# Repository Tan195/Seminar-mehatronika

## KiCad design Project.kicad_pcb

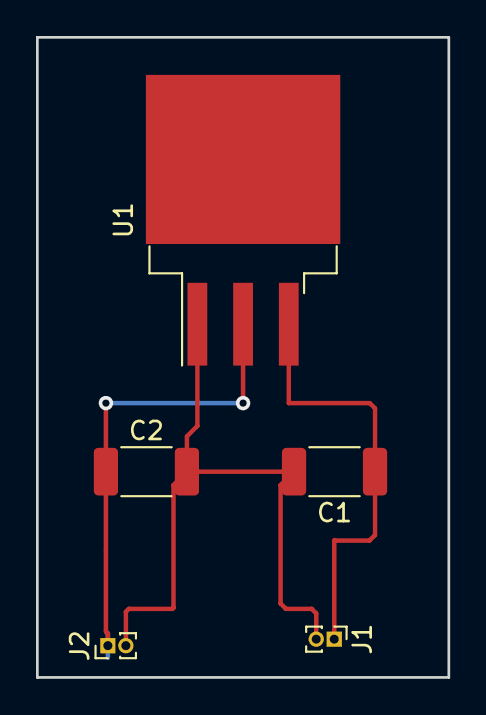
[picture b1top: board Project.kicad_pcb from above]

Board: 2 copper layers, 22.9 x 35.6 mm, 5 parts (0 on the bottom side), 3 nets.

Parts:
C1: 0,2uF; C_2010_5025Metric
C2: 0.2uF; C_2010_5025Metric
J1, J2: 0; PinHeader_1x02_P1.00mm_Vertical
U1: LM317_3PinPackage; TO-263-3_TabPin4

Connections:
unnamed: C1.1, J1.1, U1.3
unnamed: C1.2, C2.2, J1.2, J2.2, U1.1
unnamed: C2.1, J2.1, U1.2

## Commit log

2018-12-10 Zdruzen model fcad + stepup
